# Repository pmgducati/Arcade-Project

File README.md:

# Arcade-Project
Building my Own Arcade

I have been working on some variation of an arcade cabinet that for some reason or another that never came to be... Until now!

I designed the cabinet in Solidworks and the PCBs in Eagle, I have included cultists, detailed drawings, BOM’s for purchased parts, datasheets, and pretty much any other info you would need to make the cabinet.  

I also generated STLs and Gerbers for anyone that doesn't have access to them fancy CAD programs.

Shout out to my friends Rob and Rufino for helping me out with the Artwork and CNC/wood working!

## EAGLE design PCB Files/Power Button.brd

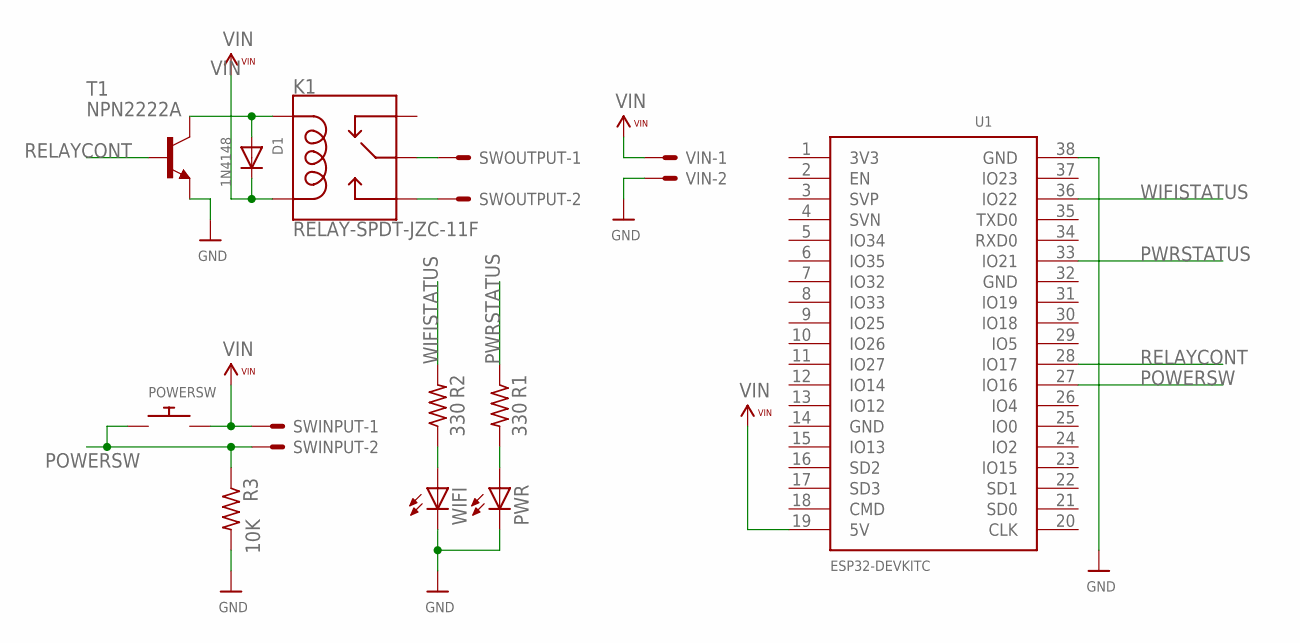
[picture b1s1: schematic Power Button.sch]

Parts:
D1: 1N4148; DO-1N4148
K1: RELAY-SPDT-JZC-11F; RELAY-JZC
POWERSW: SWITCH_PUSHBUTTONEVQ-PE; TACT_PANA-EVQ
PWR: LEDCHIPLED_1206; CHIPLED_1206
R1, R2: 330; M1206
R3: 10K; M1206
SWINPUT: KK-156-2
SWOUTPUT: KK-156-2
T1: NPN2222A; TO92
U1: ESP32DEVKITC; ESP32-DEVKITC
VIN: KK-156-2
WIFI: LEDCHIPLED_1206; CHIPLED_1206

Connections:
GND: PWR.C, R3.2, T1.3 (E), U1.38 (GND), VIN.2, WIFI.C
unnamed: R2.1, WIFI.A
unnamed: PWR.A, R1.2
POWERSW: POWERSW.P$1, R3.1, SWINPUT.2, U1.27 (IO16)
PWRSTATUS: R1.1, U1.33 (IO21)
RELAY1: K1.4 (MAIN), SWOUTPUT.1
RELAY2: K1.3 (NO), SWOUTPUT.2
RELAYCONT: T1.2 (B), U1.28 (IO17)
RELAYSW: D1.A, K1.5 (COIL1), T1.1 (C)
VIN: D1.C, K1.1 (COIL2), POWERSW.P$2, SWINPUT.1, U1.19 (5V), VIN.1
WIFISTATUS: R2.2, U1.36 (IO22)

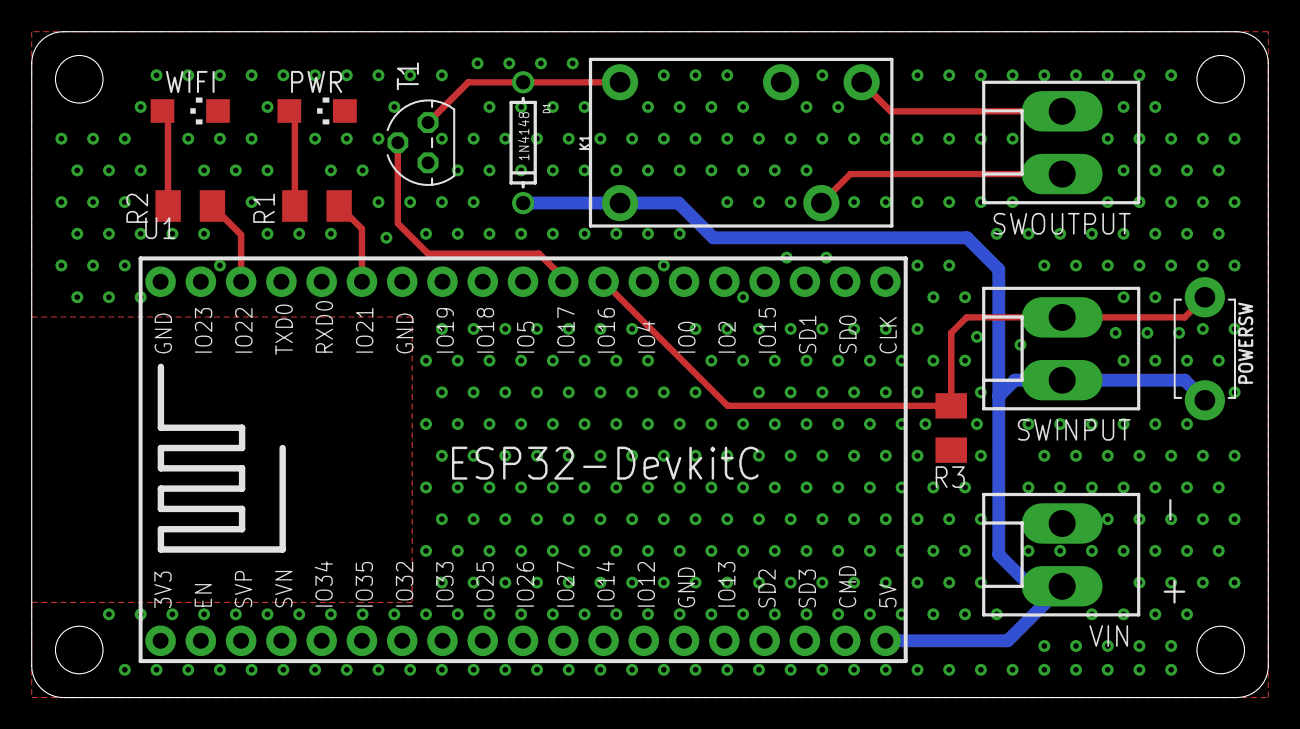
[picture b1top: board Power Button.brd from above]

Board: 2 copper layers, 78.0 x 42.0 mm, 13 parts (0 on the bottom side), 11 nets.

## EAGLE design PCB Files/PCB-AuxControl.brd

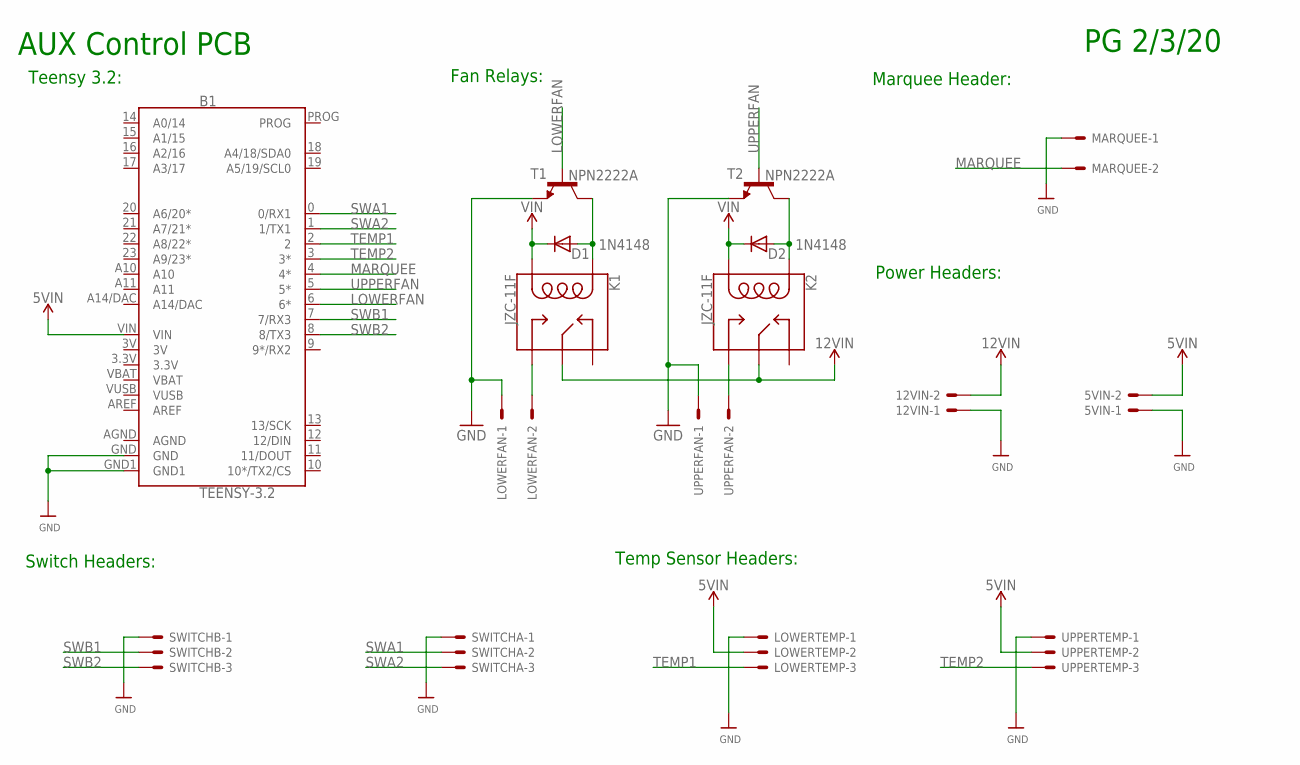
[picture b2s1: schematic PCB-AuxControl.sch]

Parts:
5VIN, 12VIN: KK-156-2
B1: TEENSY-3.2; TEENSY-3.1
D1, D2: 1N4148; DO35-7
K1, K2: JZC-11F; RELAY-JZC
LOWERFAN: KK-156-2
LOWERTEMP: KK-156-3
MARQUEE: KK-156-2
SWITCHA: KK-156-3
SWITCHB: KK-156-3
T1, T2: NPN2222A; TO92
UPPERFAN: KK-156-2
UPPERTEMP: KK-156-3

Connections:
3.3V: B1.3.3V
3V: B1.3V
5VIN: 5VIN.2, B1.VIN, D1.C, D2.C, K1.1 (COIL2), K2.1 (COIL2), LOWERTEMP.2, MARQUEE.3, UPPERTEMP.2; also elsewhere on the board
12VIN: 12VIN.2, K1.4 (MAIN), K2.4 (MAIN)
AGND: B1.AGND
CLK: B1.19 (A5/19/SCL0); also elsewhere on the board
DAT: B1.18 (A4/18/SDA0); also elsewhere on the board
GND: 5VIN.1, 12VIN.1, B1.GND, B1.GND1, LOWERFAN.1, LOWERTEMP.1, MARQUEE.1, SWITCHA.1, SWITCHB.1, T1.1 (E), T2.1 (E), UPPERFAN.1, UPPERTEMP.1; also elsewhere on the board
LOWERFAN: B1.6 (6*), T1.2 (B)
MARQUEE: B1.4 (4*), MARQUEE.2
unnamed: K2.3 (NO), UPPERFAN.2
unnamed: K1.3 (NO), LOWERFAN.2
RELAY1: D1.A, K1.5 (COIL1), T1.3 (C)
RELAY2: D2.A, K2.5 (COIL1), T2.3 (C)
SWA1: B1.0 (0/RX1), SWITCHA.2
SWA2: B1.1 (1/TX1), SWITCHA.3
SWB1: B1.7 (7/RX3), SWITCHB.2
SWB2: B1.8 (8/TX3), SWITCHB.3
TEMP1: B1.2, LOWERTEMP.3
TEMP2: B1.3 (3*), UPPERTEMP.3
UPPERFAN: B1.5 (5*), T2.2 (B)
VBAT: B1.VBAT
VUSB: B1.VUSB

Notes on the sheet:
Teensy 3.2:
Switch Headers:
Temp Sensor Headers:
Power Headers:
Marquee Header:
Fan Relays:
AUX Control PCB
PG 2/3/20

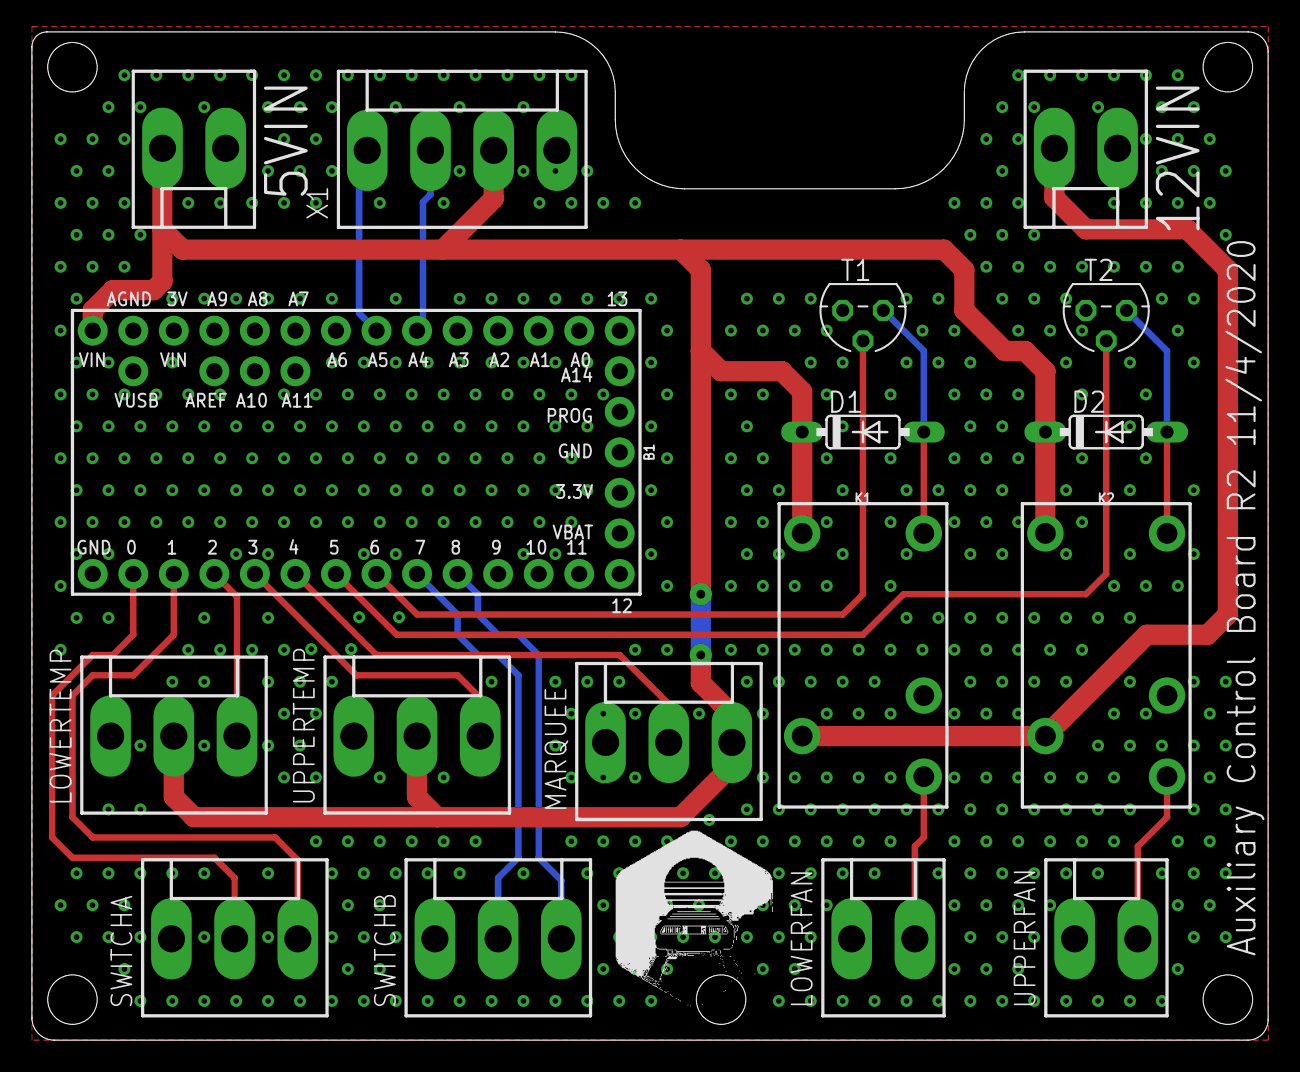
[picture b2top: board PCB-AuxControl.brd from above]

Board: 2 copper layers, 77.5 x 63.2 mm, 17 parts (0 on the bottom side), 18 nets.

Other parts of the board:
X1: KK-156-4

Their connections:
5VIN: X1.3; also elsewhere on the board
CLK: X1.1; also elsewhere on the board
DAT: X1.2; also elsewhere on the board
GND: X1.4; also elsewhere on the board

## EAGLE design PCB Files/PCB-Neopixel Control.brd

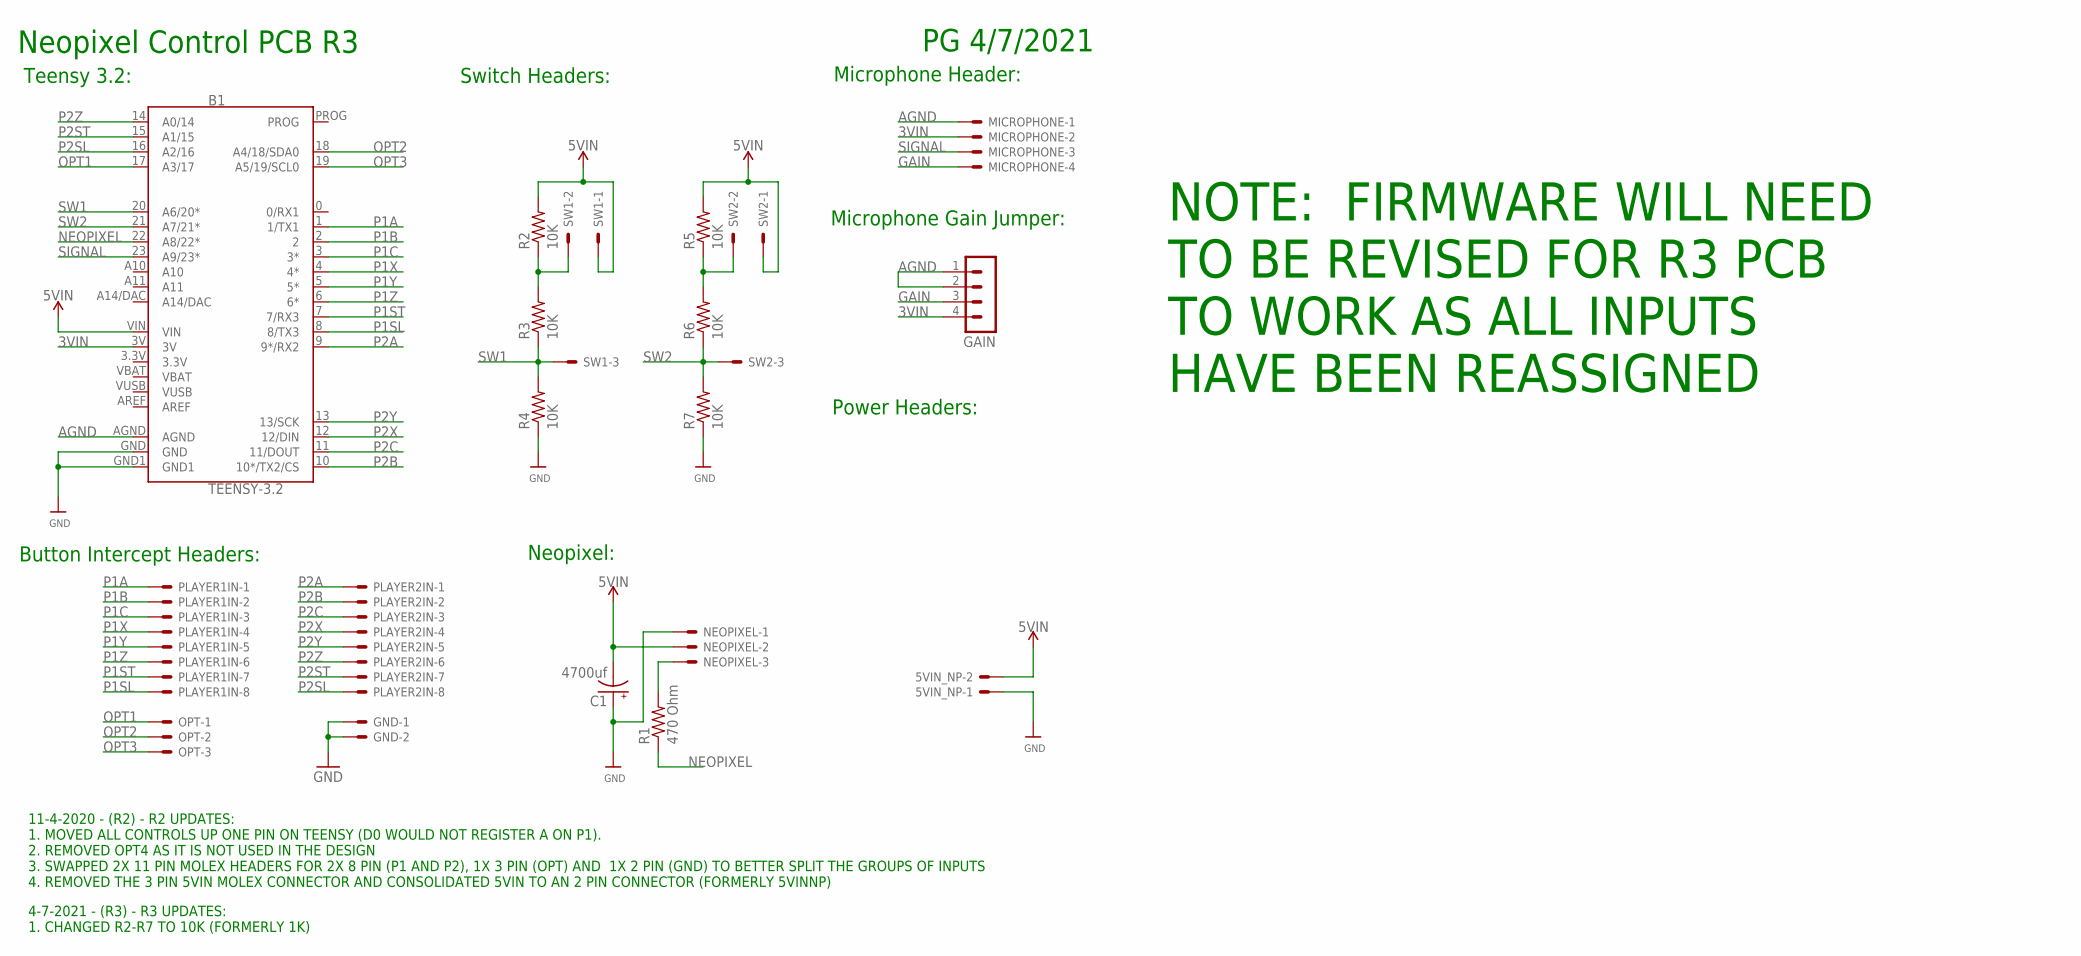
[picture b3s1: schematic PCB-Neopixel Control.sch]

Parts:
5VIN_NP: KK-156-2
B1: TEENSY-3.2; TEENSY-3.1
C1: 4700uf; E5-13
GAIN: MA04-1
GND: KK-156-2
MICROPHONE: KK-156-4
NEOPIXEL: KK-156-3
OPT: KK-156-3
PLAYER1IN, PLAYER2IN: KK-156-8
R1: 470 Ohm; R1206
R2, R3, R4, R5, R6, R7: 10K; R1206
SW1, SW2: KK-156-3

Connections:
3.3V: B1.3.3V
3VIN: B1.3V, GAIN.4, MICROPHONE.2
5VIN: 5VIN_NP.2, B1.VIN, C1.-, NEOPIXEL.2, R2.2, R5.2, SW1.1, SW2.1
AGND: B1.AGND, GAIN.1, GAIN.2, MICROPHONE.1
GAIN: GAIN.3, MICROPHONE.4
GND: 5VIN_NP.1, B1.GND, B1.GND1, C1.+, GND.1, GND.2, NEOPIXEL.1, R4.1, R7.1
NEOPIXEL: B1.22 (A8/22*), R1.1
NP2T: NEOPIXEL.3, R1.2
OPT1: B1.17 (A3/17), OPT.1
OPT2: B1.18 (A4/18/SDA0), OPT.2
OPT3: B1.19 (A5/19/SCL0), OPT.3
P1A: B1.1 (1/TX1), PLAYER1IN.1
P1B: B1.2, PLAYER1IN.2
P1C: B1.3 (3*), PLAYER1IN.3
P1SL: B1.8 (8/TX3), PLAYER1IN.8
P1ST: B1.7 (7/RX3), PLAYER1IN.7
P1X: B1.4 (4*), PLAYER1IN.4
P1Y: B1.5 (5*), PLAYER1IN.5
P1Z: B1.6 (6*), PLAYER1IN.6
P2A: B1.9 (9*/RX2), PLAYER2IN.1
P2B: B1.10 (10*/TX2/CS), PLAYER2IN.2
P2C: B1.11 (11/DOUT), PLAYER2IN.3
P2SL: B1.16 (A2/16), PLAYER2IN.8
P2ST: B1.15 (A1/15), PLAYER2IN.7
P2X: B1.12 (12/DIN), PLAYER2IN.4
P2Y: B1.13 (13/SCK), PLAYER2IN.5
P2Z: B1.14 (A0/14), PLAYER2IN.6
SIGNAL: B1.23 (A9/23*), MICROPHONE.3
SW1: B1.20 (A6/20*), R3.1, R4.2, SW1.3
SW1A: R2.1, R3.2, SW1.2
SW2: B1.21 (A7/21*), R6.1, R7.2, SW2.3
SW2A: R5.1, R6.2, SW2.2
VBAT: B1.VBAT
VUSB: B1.VUSB

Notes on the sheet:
Teensy 3.2:
Switch Headers:
Microphone Header:
Microphone Gain Jumper:
Power Headers:
Neopixel:
Button Intercept Headers:
Neopixel Control PCB R3
PG 4/7/2021
11-4-2020 - (R2) - R2 UPDATES: 1. MOVED ALL CONTROLS UP ONE PIN ON TEENSY (D0 WOULD NOT REGISTER A ON P1). 2. REMOVED OPT4 AS IT IS NOT USED IN THE DESIGN 3. SWAPPED 2X 11 PIN MOLEX HEADERS FOR 2X 8 PIN (P1 AND P2), 1X 3 PIN (OPT) AND 1X 2 PIN (GND) TO BETTER SPLIT THE GROUPS OF INPUTS 4. REMOVED T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
NOTE: FIRMWARE WILL NEED TO BE REVISED FOR R3 PCB TO WORK AS ALL INPUTS HAVE BEEN REASSIGNED
4-7-2021 - (R3) - R3 UPDATES: 1. CHANGED R2-R7 TO 10K (FORMERLY 1K)

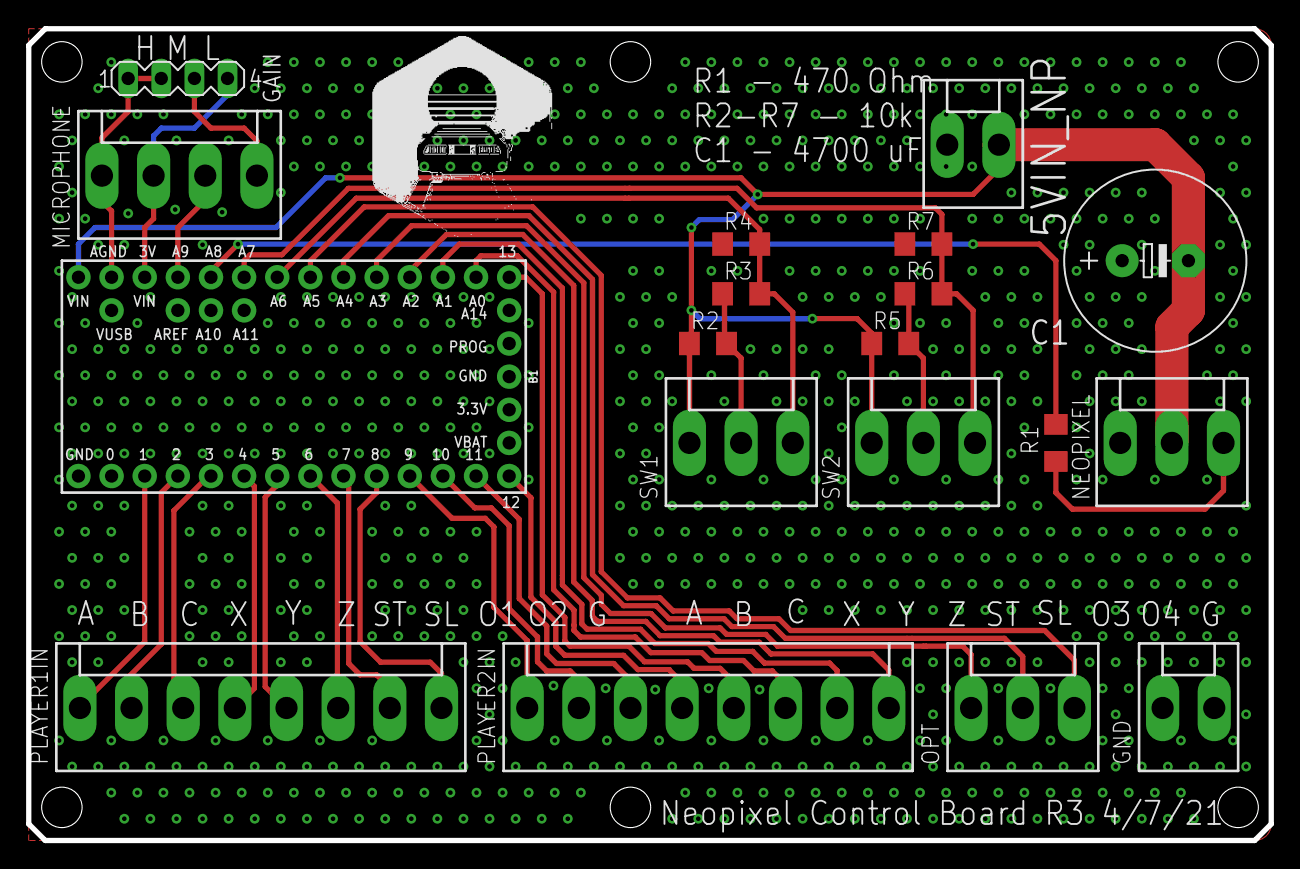
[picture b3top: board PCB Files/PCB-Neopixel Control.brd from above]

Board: 2 copper layers, 95.2 x 62.2 mm, 19 parts (0 on the bottom side), 31 nets.

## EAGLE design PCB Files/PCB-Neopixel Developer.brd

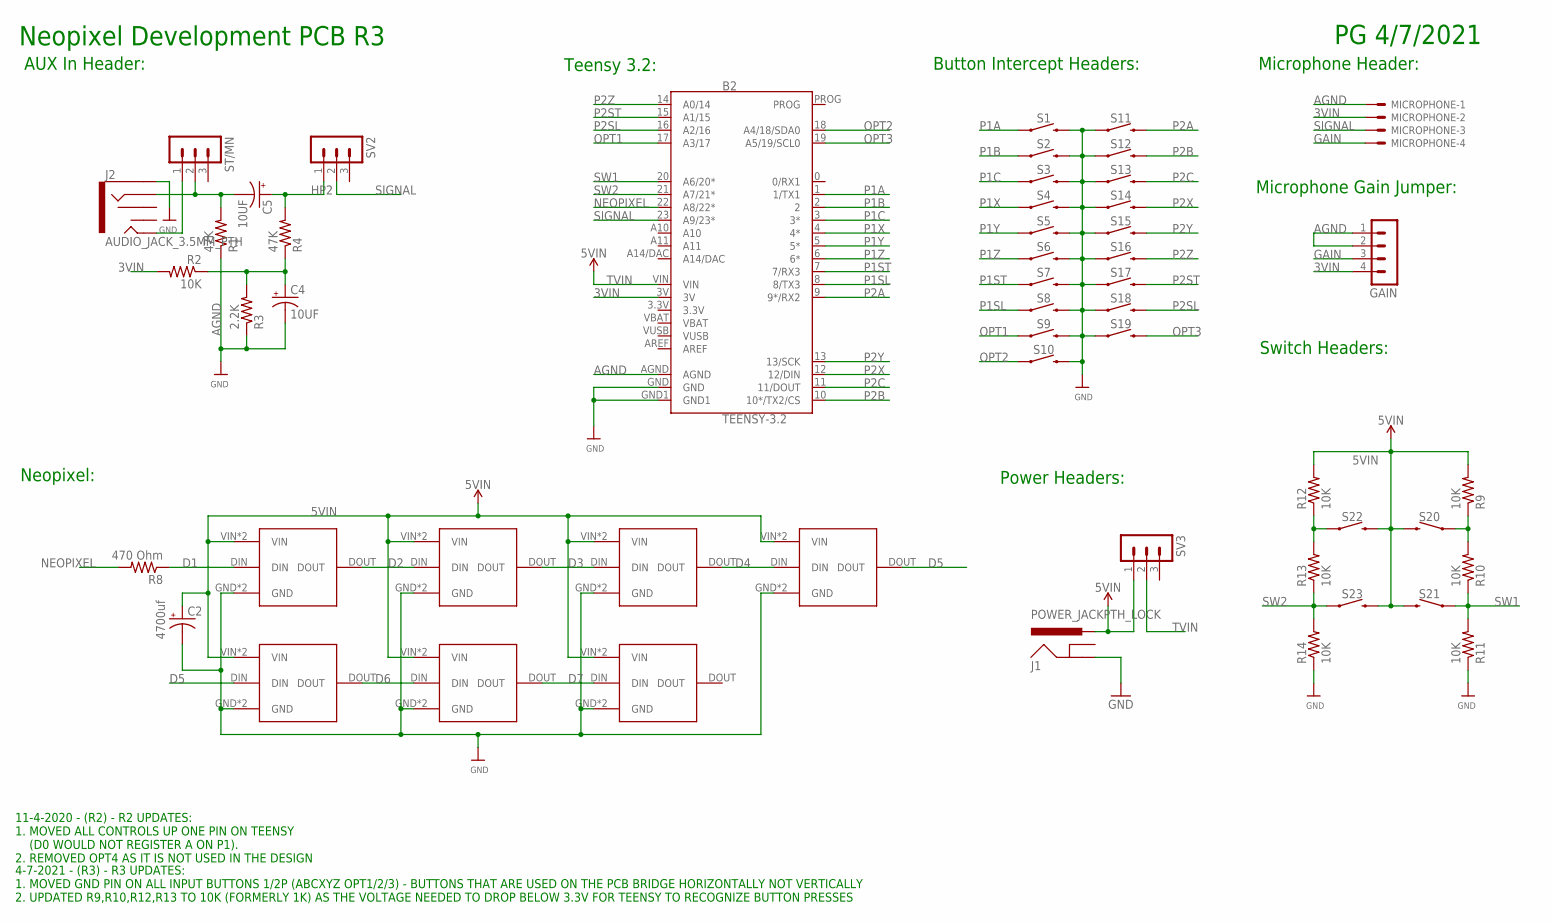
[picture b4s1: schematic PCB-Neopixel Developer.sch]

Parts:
B2: TEENSY-3.2; TEENSY-3.1
C2: 4700uf; E5-13
C4, C5: 10UF; E5-8,5
GAIN: MA04-1
J1: POWER_JACKPTH_LOCK; POWER_JACK_PTH_LOCK
J2: AUDIO_JACK_3.5MM_PTH; AUDIO-JACK
MICROPHONE: KK-156-4
R1, R4: 47K; R1206
R2, R9, R10, R11, R12, R13, R14: 10K; R1206
R3: 2.2K; R1206
R8: 470 Ohm; R1206
S1, S2, S3, S4, S5, S6, S7, S8, S9, S10, S11, S12, S13, S14, S15, S16, S17, S18, S19: MOMENTARY-SWITCH-SPST-SMD-6.2MM-TALL; TACTILE_SWITCH_SMD_6.2MM_TALL
S20, S21, S22, S23: MOMENTARY-SWITCH-SPST-PTH-6.0MM; TACTILE_SWITCH_PTH_6.0MM
ST/MN: MA03-1
SV2, SV3: MA03-1
U$2, U$7: NP-2
U$8, U$10, U$11, U$12, U$13: NP-3

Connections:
3.3V: B2.3.3V
3VIN: B2.3V, GAIN.4, MICROPHONE.2, R2.2
5VIN: C2.+, J1.PWR, R9.2, R12.2, S20.3 (2), S21.3 (2), S22.3 (2), S23.3 (2), SV3.1, U$2.VIN, U$2.VOUT (VIN), U$7.VIN, U$7.VOUT (VIN), U$8.VIN, U$8.VOUT (VIN), U$10.VIN, U$10.VOUT (VIN), U$11.VIN, U$11.VOUT (VIN), U$12.VIN, U$12.VOUT (VIN), U$13.VIN, U$13.VOUT (VIN)
AGND: B2.AGND, C4.-, GAIN.1, GAIN.2, J2.SLEEVE, MICROPHONE.1, R1.1, R3.1
D1: R8.1, U$12.DIN
D2: U$12.DOUT, U$13.DIN
D3: U$2.DIN, U$13.DOUT
D4: U$2.DOUT, U$11.DIN
D5: U$7.DIN, U$11.DOUT
D6: U$7.DOUT, U$8.DIN
D7: U$8.DOUT, U$10.DIN
GAIN: GAIN.3, MICROPHONE.4
GND: B2.GND, B2.GND1, C2.-, J1.GND, R11.1, R14.1, S1.A1 (2), S2.A1 (2), S3.A1 (2), S4.A1 (2), S5.A1 (2), S6.A1 (2), S7.A1 (2), S8.A1 (2), S9.A1 (2), S10.A1 (2), S11.A2 (1), S12.A2 (1), S13.A2 (1), S14.A2 (1), S15.A2 (1), S16.A2 (1), S17.A2 (1), S18.A2 (1), S19.A2 (1), U$2.GND, U$2.GND1 (GND), U$7.GND, U$7.GND1 (GND), U$8.GND, U$8.GND1 (GND), U$10.GND, U$10.GND1 (GND), U$11.GND, U$11.GND1 (GND), U$12.GND, U$12.GND1 (GND), U$13.GND, U$13.GND1 (GND)
HP1: C4.+, R2.1, R3.2, R4.1
HP2: C5.+, R4.2, SV2.1
unnamed: J2.TIP, ST/MN.1
unnamed: C5.-, J2.RING, R1.2, ST/MN.2
NEOPIXEL: B2.22 (A8/22*), R8.2
OPT1: B2.17 (A3/17), S9.A2 (1)
OPT2: B2.18 (A4/18/SDA0), S10.A2 (1)
OPT3: B2.19 (A5/19/SCL0), S19.A1 (2)
P1A: B2.1 (1/TX1), S1.A2 (1)
P1B: B2.2, S2.A2 (1)
P1C: B2.3 (3*), S3.A2 (1)
P1SL: B2.8 (8/TX3), S8.A2 (1)
P1ST: B2.7 (7/RX3), S7.A2 (1)
P1X: B2.4 (4*), S4.A2 (1)
P1Y: B2.5 (5*), S5.A2 (1)
P1Z: B2.6 (6*), S6.A2 (1)
P2A: B2.9 (9*/RX2), S11.A1 (2)
P2B: B2.10 (10*/TX2/CS), S12.A1 (2)
P2C: B2.11 (11/DOUT), S13.A1 (2)
P2SL: B2.16 (A2/16), S18.A1 (2)
P2ST: B2.15 (A1/15), S17.A1 (2)
P2X: B2.12 (12/DIN), S14.A1 (2)
P2Y: B2.13 (13/SCK), S15.A1 (2)
P2Z: B2.14 (A0/14), S16.A1 (2)
SIGNAL: B2.23 (A9/23*), MICROPHONE.3, SV2.2
SW1: B2.20 (A6/20*), R10.1, R11.2, S21.1
SW1A: R9.1, R10.2, S20.1
SW2: B2.21 (A7/21*), R13.1, R14.2, S23.1
SW2A: R12.1, R13.2, S22.1
TVIN: B2.VIN, SV3.2
VBAT: B2.VBAT
VUSB: B2.VUSB

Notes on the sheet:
Teensy 3.2:
Switch Headers:
Microphone Header:
Microphone Gain Jumper:
Power Headers:
Neopixel:
Button Intercept Headers:
Neopixel Development PCB R3
PG 4/7/2021
AUX In Header:
11-4-2020 - (R2) - R2 UPDATES: 1. MOVED ALL CONTROLS UP ONE PIN ON TEENSY (D0 WOULD NOT REGISTER A ON P1). 2. REMOVED OPT4 AS IT IS NOT USED IN THE DESIGN
4-7-2021 - (R3) - R3 UPDATES: 1. MOVED GND PIN ON ALL INPUT BUTTONS 1/2P (ABCXYZ OPT1/2/3) - BUTTONS THAT ARE USED ON THE PCB BRIDGE HORIZONTALLY NOT VERTICALLY 2. UPDATED R9,R10,R12,R13 TO 10K (FORMERLY 1K) AS THE VOLTAGE NEEDED TO DROP BELOW 3.3V FOR TEENSY TO RECOGNIZE BUTTON PRESSES

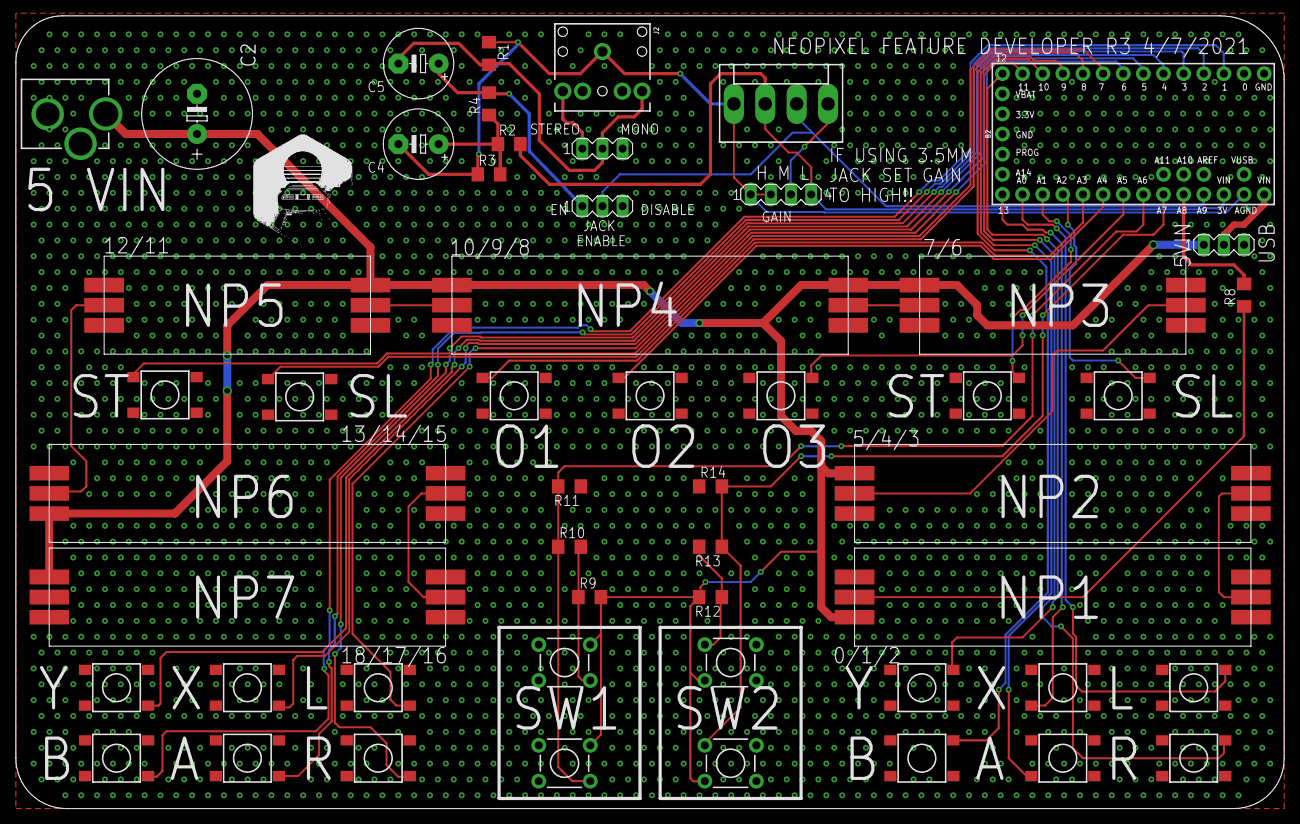
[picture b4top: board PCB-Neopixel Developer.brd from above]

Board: 2 copper layers, 160.0 x 100.0 mm, 52 parts (0 on the bottom side), 42 nets.

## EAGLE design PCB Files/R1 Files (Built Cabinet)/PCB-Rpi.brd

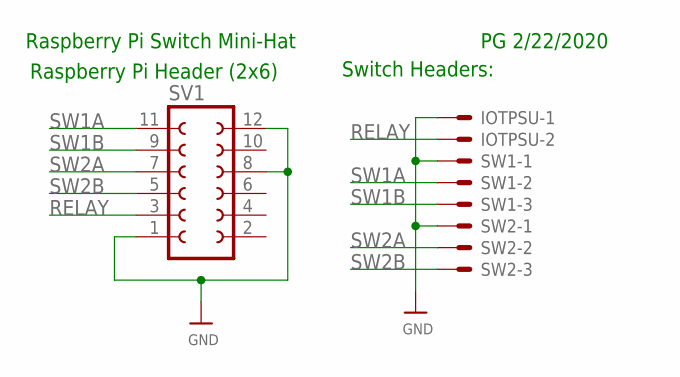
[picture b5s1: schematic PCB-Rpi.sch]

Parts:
IOTPSU: KK-156-2
SV1: FE06-2
SW1, SW2: KK-156-3

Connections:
GND: IOTPSU.1, SV1.1, SV1.8, SV1.12, SW1.1, SW2.1
RELAY: IOTPSU.2, SV1.3
SW1A: SV1.11, SW1.2
SW1B: SV1.9, SW1.3
SW2A: SV1.7, SW2.2
SW2B: SV1.5, SW2.3

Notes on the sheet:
Switch Headers:
Raspberry Pi Header (2x6)
Raspberry Pi Switch Mini-Hat
PG 2/22/2020

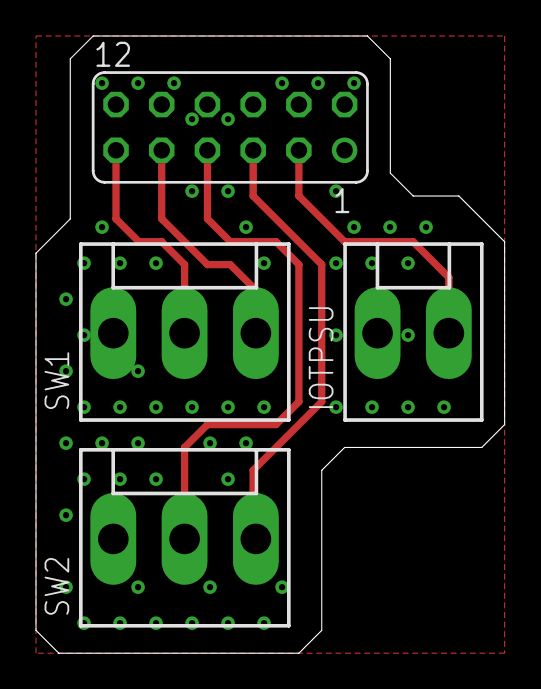
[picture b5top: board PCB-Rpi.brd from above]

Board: 2 copper layers, 26.0 x 34.3 mm, 4 parts (0 on the bottom side), 6 nets.

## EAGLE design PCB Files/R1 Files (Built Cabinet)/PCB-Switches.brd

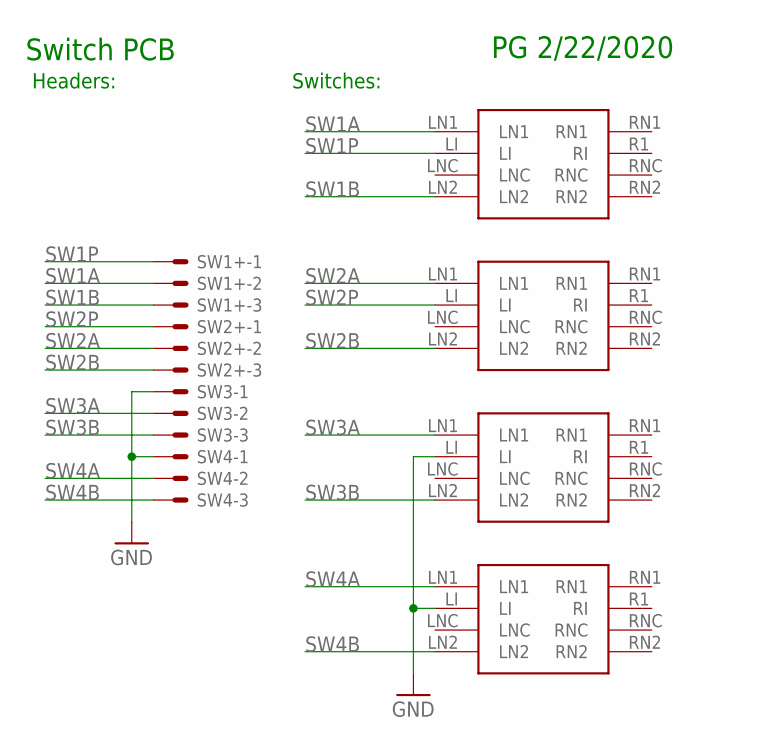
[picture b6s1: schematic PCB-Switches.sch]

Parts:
SW1+, SW2+, SW3, SW4: KK-156-3
U$1, U$2, U$3, U$4: ARCADESWITCH

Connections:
GND: SW3.1, SW4.1, U$3.LI, U$4.LI
SW1A: SW1+.2, U$1.LN1
SW1B: SW1+.3, U$1.LN2
SW1P: SW1+.1, U$1.LI
SW2A: SW2+.2, U$2.LN1
SW2B: SW2+.3, U$2.LN2
SW2P: SW2+.1, U$2.LI
SW3A: SW3.2, U$3.LN1
SW3B: SW3.3, U$3.LN2
SW4A: SW4.2, U$4.LN1
SW4B: SW4.3, U$4.LN2

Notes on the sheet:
Switches:
Headers:
Switch PCB
PG 2/22/2020

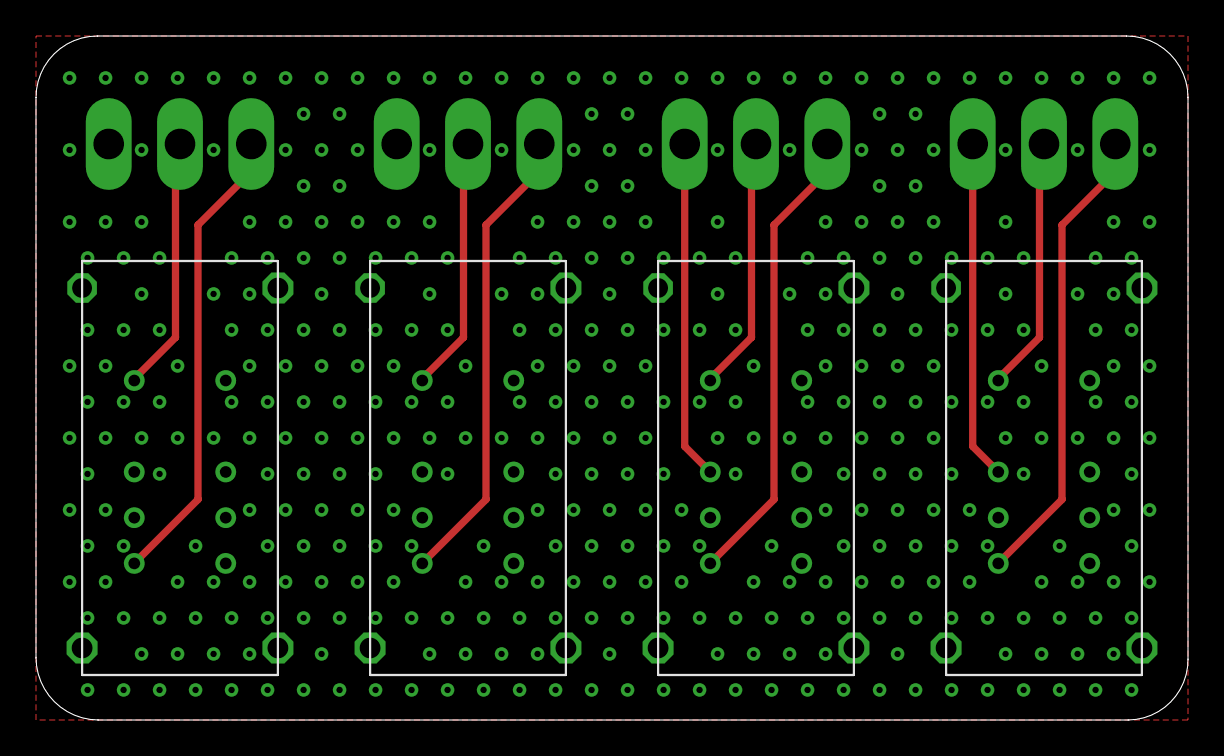
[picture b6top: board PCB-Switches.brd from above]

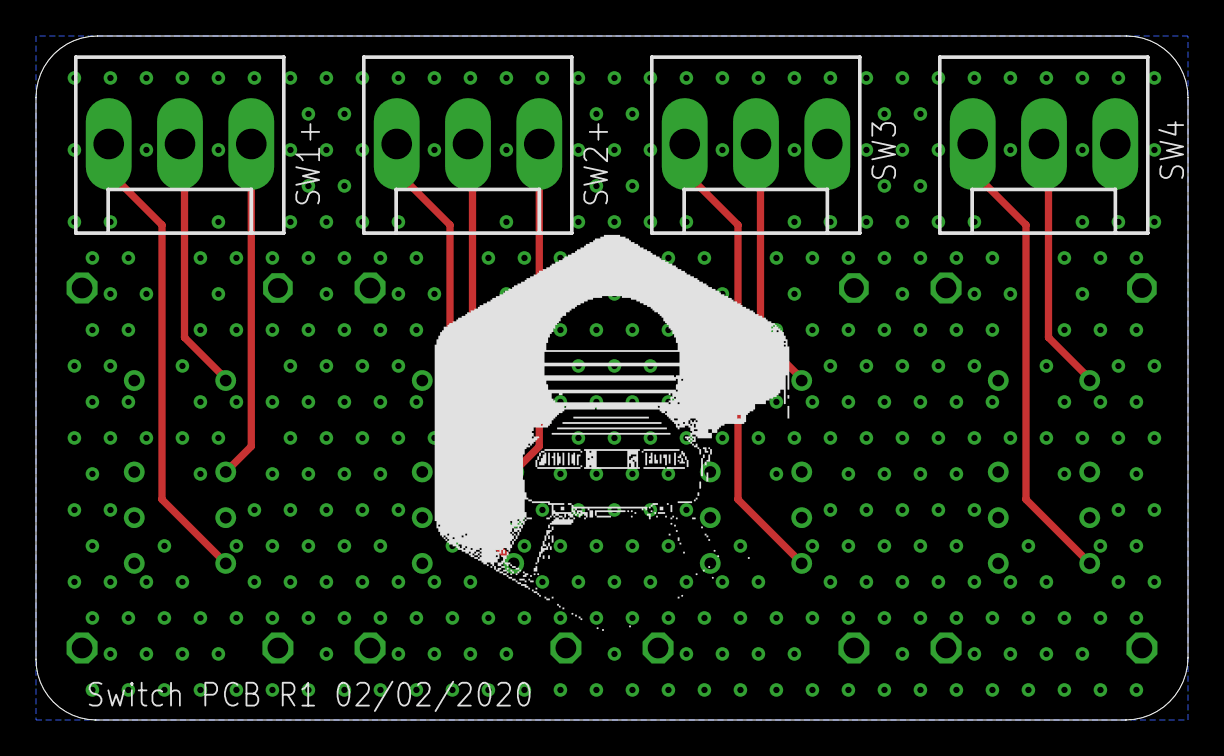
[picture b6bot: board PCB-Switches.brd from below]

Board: 2 copper layers, 64.0 x 38.0 mm, 8 parts (4 on the bottom side), 11 nets.

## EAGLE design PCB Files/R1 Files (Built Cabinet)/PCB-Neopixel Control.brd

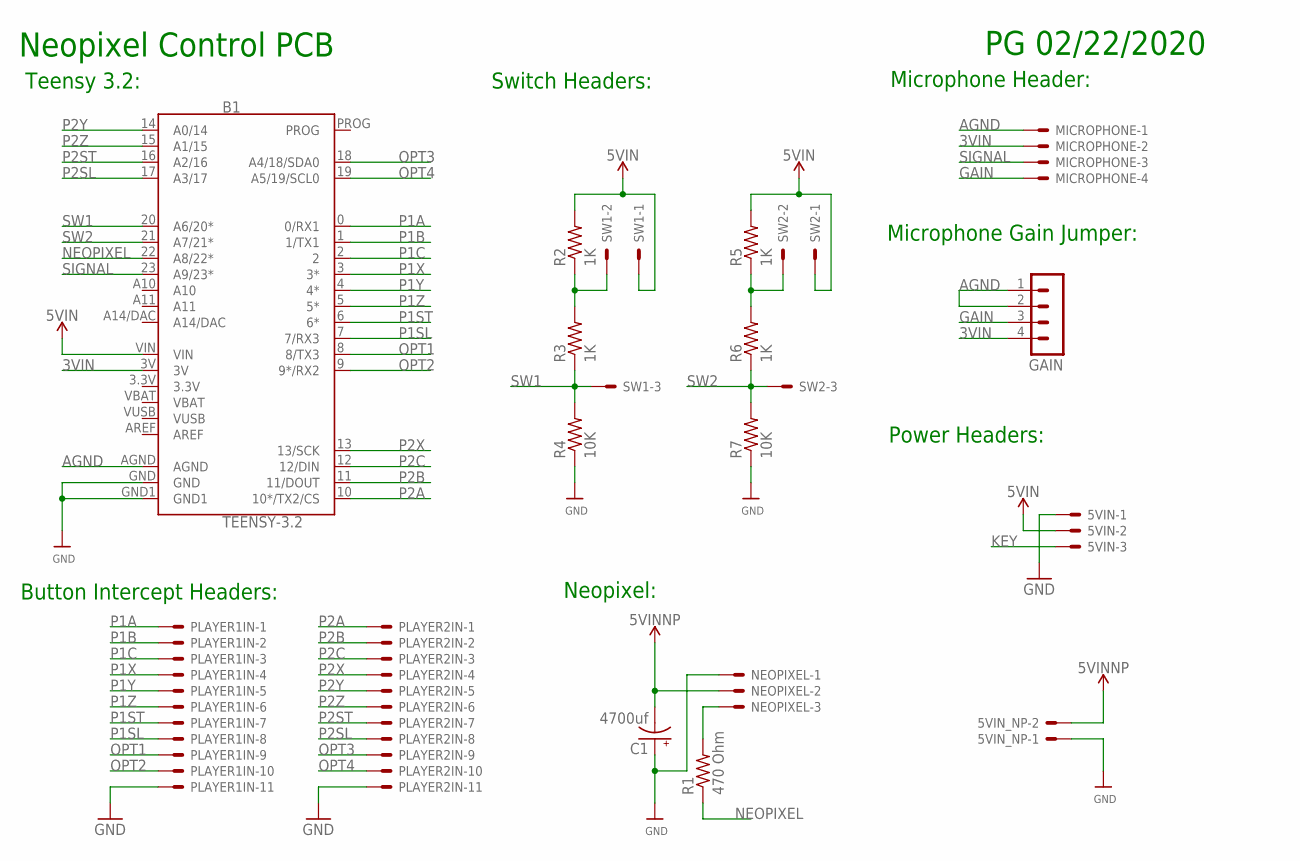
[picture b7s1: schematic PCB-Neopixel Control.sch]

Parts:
5VIN: KK-156-3
5VIN_NP: KK-156-2
B1: TEENSY-3.2; TEENSY-3.1
C1: 4700uf; E5-13
GAIN: MA04-1
MICROPHONE: KK-156-4
NEOPIXEL: KK-156-3
PLAYER1IN, PLAYER2IN: KK-156-11
R1: 470 Ohm; R1206
R2, R3, R5, R6: 1K; R1206
R4, R7: 10K; R1206
SW1, SW2: KK-156-3

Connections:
3.3V: B1.3.3V
3VIN: B1.3V, GAIN.4, MICROPHONE.2
5VIN: 5VIN.2, B1.VIN, R2.2, R5.2, SW1.1, SW2.1
5VINNP: 5VIN_NP.2, C1.-, NEOPIXEL.2
AGND: B1.AGND, GAIN.1, GAIN.2, MICROPHONE.1
GAIN: GAIN.3, MICROPHONE.4
GND: 5VIN.1, 5VIN_NP.1, B1.GND, B1.GND1, C1.+, NEOPIXEL.1, PLAYER1IN.11, PLAYER2IN.11, R4.1, R7.1
KEY: 5VIN.3
NEOPIXEL: B1.22 (A8/22*), R1.1
NP2T: NEOPIXEL.3, R1.2
OPT1: B1.8 (8/TX3), PLAYER1IN.9
OPT2: B1.9 (9*/RX2), PLAYER1IN.10
OPT3: B1.18 (A4/18/SDA0), PLAYER2IN.9
OPT4: B1.19 (A5/19/SCL0), PLAYER2IN.10
P1A: B1.0 (0/RX1), PLAYER1IN.1
P1B: B1.1 (1/TX1), PLAYER1IN.2
P1C: B1.2, PLAYER1IN.3
P1SL: B1.7 (7/RX3), PLAYER1IN.8
P1ST: B1.6 (6*), PLAYER1IN.7
P1X: B1.3 (3*), PLAYER1IN.4
P1Y: B1.4 (4*), PLAYER1IN.5
P1Z: B1.5 (5*), PLAYER1IN.6
P2A: B1.10 (10*/TX2/CS), PLAYER2IN.1
P2B: B1.11 (11/DOUT), PLAYER2IN.2
P2C: B1.12 (12/DIN), PLAYER2IN.3
P2SL: B1.17 (A3/17), PLAYER2IN.8
P2ST: B1.16 (A2/16), PLAYER2IN.7
P2X: B1.13 (13/SCK), PLAYER2IN.4
P2Y: B1.14 (A0/14), PLAYER2IN.5
P2Z: B1.15 (A1/15), PLAYER2IN.6
SIGNAL: B1.23 (A9/23*), MICROPHONE.3
SW1: B1.20 (A6/20*), R3.1, R4.2, SW1.3
SW1A: R2.1, R3.2, SW1.2
SW2: B1.21 (A7/21*), R6.1, R7.2, SW2.3
SW2A: R5.1, R6.2, SW2.2
VBAT: B1.VBAT
VUSB: B1.VUSB

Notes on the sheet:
Teensy 3.2:
Switch Headers:
Microphone Header:
Microphone Gain Jumper:
Power Headers:
Neopixel:
Button Intercept Headers:
Neopixel Control PCB
PG 02/22/2020

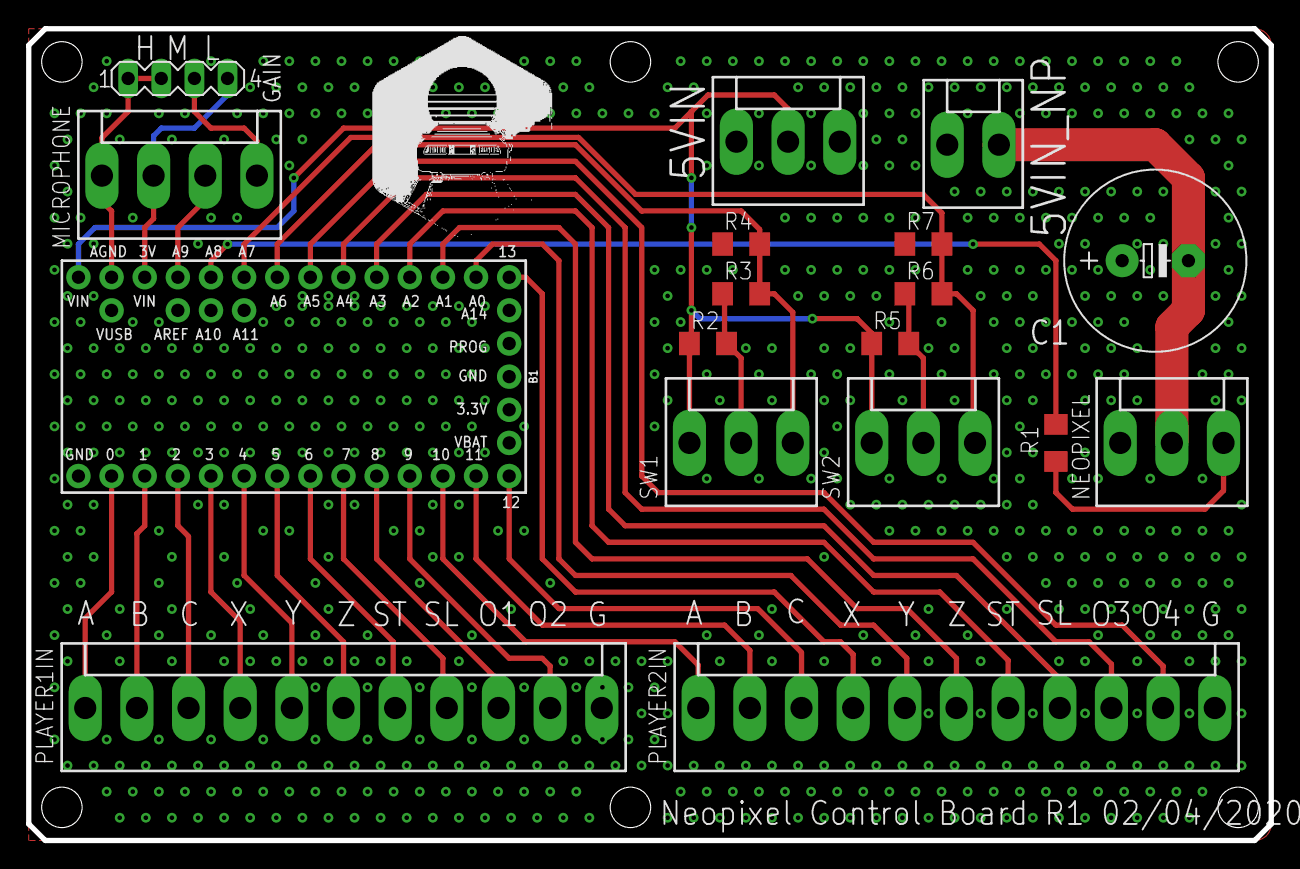
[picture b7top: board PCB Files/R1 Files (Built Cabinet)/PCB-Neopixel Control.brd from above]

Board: 2 copper layers, 95.2 x 62.2 mm, 18 parts (0 on the bottom side), 33 nets.

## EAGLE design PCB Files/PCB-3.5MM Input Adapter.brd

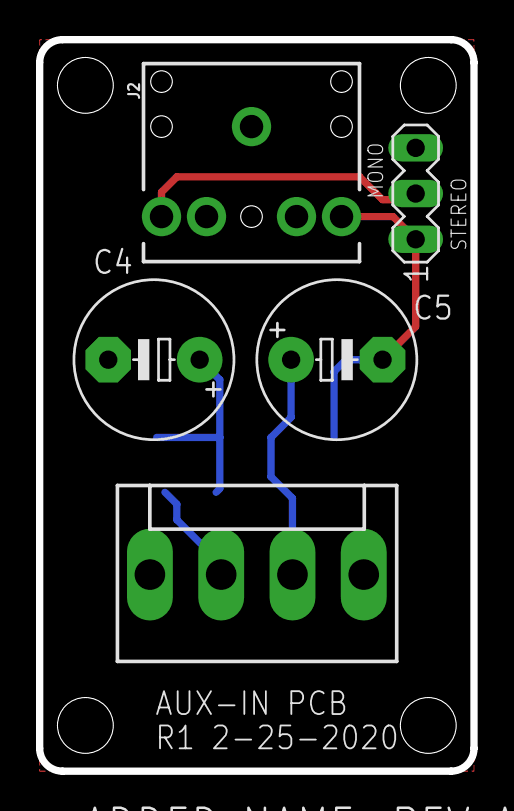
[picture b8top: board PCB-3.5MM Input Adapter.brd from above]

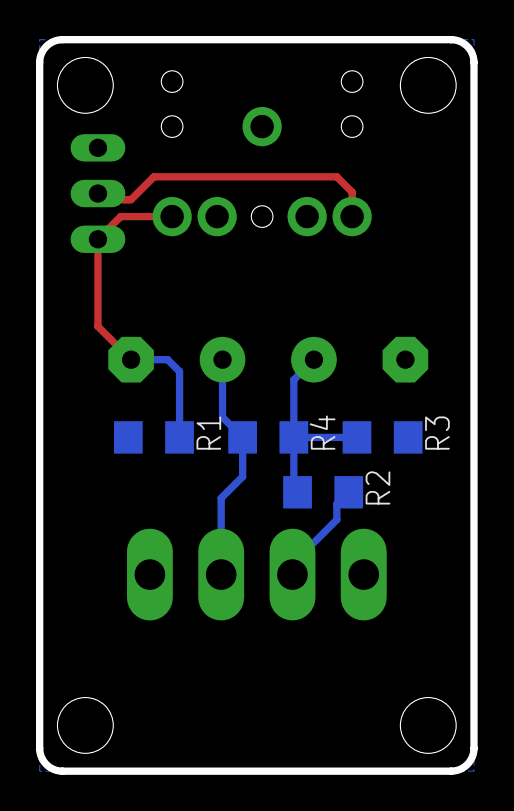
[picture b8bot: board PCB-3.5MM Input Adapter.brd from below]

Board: 2 copper layers, 24.1 x 40.6 mm, 9 parts (4 on the bottom side), 6 nets.

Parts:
C4, C5: 10UF; E5-8,5
HEADER: KK-156-4
J2: AUDIO_JACK_3.5MM_PTH; AUDIO-JACK
R1, R4: 47K; R1206
R2: 10K; R1206
R3: 2.2K; R1206
ST/MN: MA03-1

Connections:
3VIN: HEADER.2, R2.2
AGND: C4.-, HEADER.1, J2.SLEEVE, R1.1, R3.1
HP1: C4.+, R2.1, R3.2, R4.1
unnamed: J2.TIP, ST/MN.2
unnamed: C5.-, J2.RING, R1.2, ST/MN.1
SIGNAL: C5.+, HEADER.3, R4.2

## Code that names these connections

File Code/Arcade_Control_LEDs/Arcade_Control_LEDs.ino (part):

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#define P1_Z 6       //Player 1 Button Z
#define SW1  A6      //Toggle Switch 1y
#define SW2  A7      //Toggle Switch 2
#define DATA_PIN  22 //Neopixel Data Pin

//FastLED Parameters
#define LED_TYPE    WS2811
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  pinMode(P1_X, INPUT);     //Player 1 Button X
  pinMode(P1_Y, INPUT);     //Player 1 Button Y
  pinMode(P1_Z, INPUT);     //Player 1 Button Z
  pinMode(OPT1, INPUT);     //Option 1 (QUIT)
  pinMode(OPT2, INPUT);     //Option 2 (SAVE)
  pinMode(OPT3, INPUT);     //Option 3 (LOAD)
}

//Array Setup
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

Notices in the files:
parts and their libraries:
SparkFun-Connectors: Licensing: Creative Commons ShareAlike 4.0 International - https://creativecommons.org/licenses/by-sa/4.0
PatternAgents-Beautify: License : http://creativecommons.org/licenses/by-sa/3.0
(Creative Commons 3.0)
